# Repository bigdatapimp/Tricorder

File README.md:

This project is a compact hand held device based on the Arduino Nano 33 BLE sense Rev2 board, inspired by the Tricorder from the Star Trek Franchise
It utilzes a variety of on board sensors as well as GPS to gather a range of data.

There is no license to use this code. I would appriciate a mention if used in your own projects or if you choose to follow the build

By: Tony Dillberg
Feb 2026

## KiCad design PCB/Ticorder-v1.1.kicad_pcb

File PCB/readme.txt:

These are the current GERBER files for the PCB design, as well as the current version of the KiCAD files.

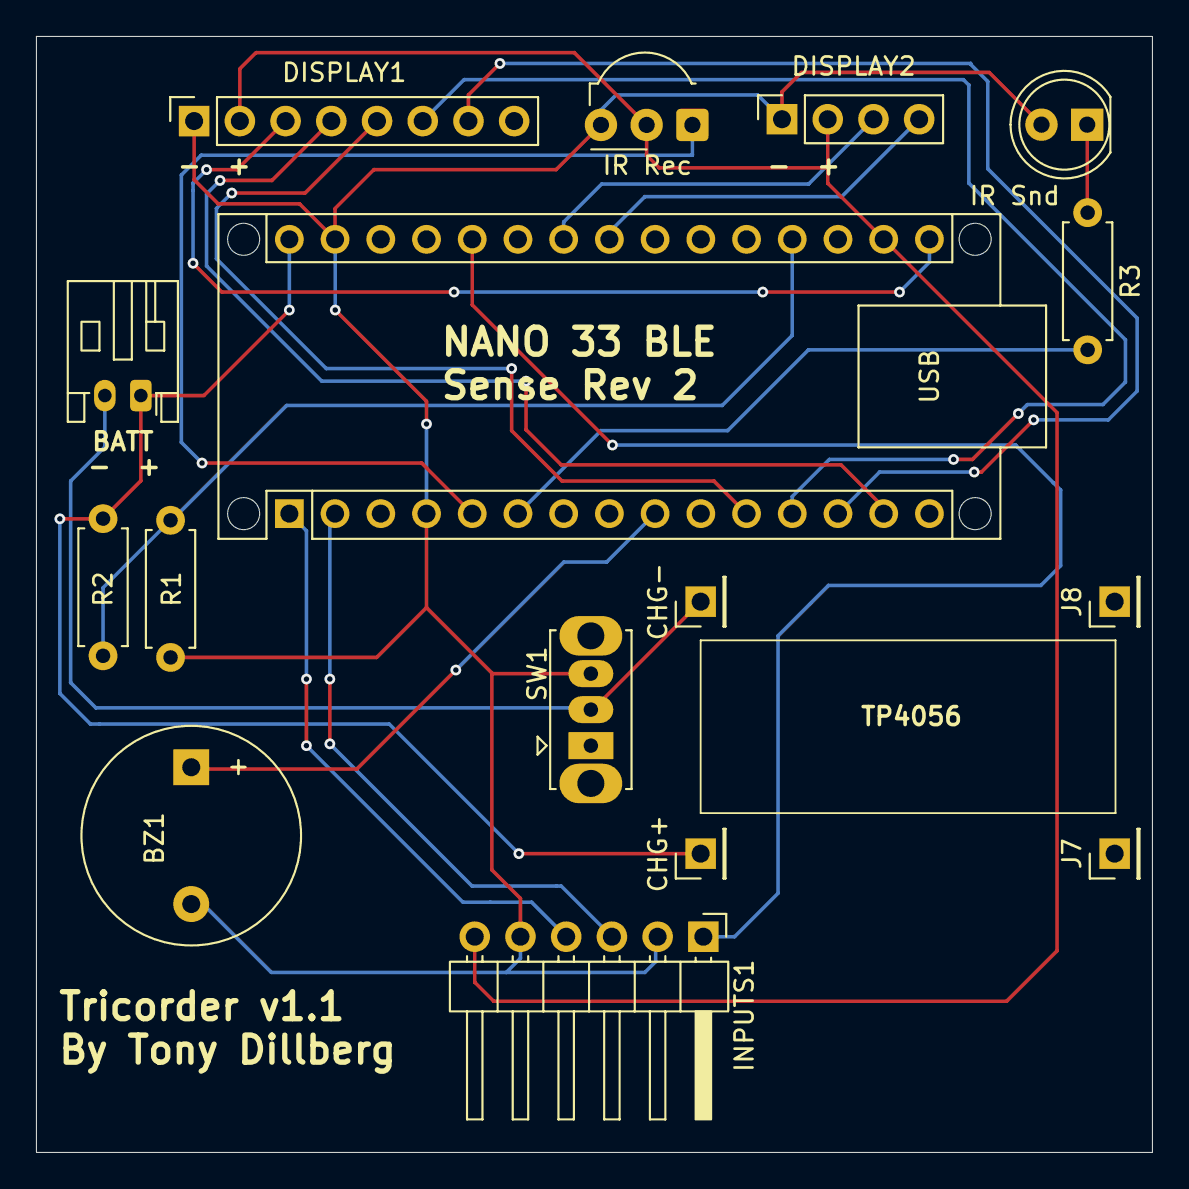
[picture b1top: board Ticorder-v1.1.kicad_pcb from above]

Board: 2 copper layers, 62.0 x 62.0 mm, 16 parts (0 on the bottom side), 19 nets.

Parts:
A1: Arduino_Nano_ESP32; Arduino_Nano_WithMountingHoles
BATT: Conn_01x02; JST_PH_S2B-PH-K_1x02_P2.00mm_Horizontal
BZ1: Buzzer; Buzzer_12x9.5RM7.6
CHG+: Conn_01x01_Pin; PinHeader_1x01_P2.54mm_Vertical
CHG-: Conn_01x01_Pin; PinHeader_1x01_P2.54mm_Vertical
DISPLAY1: Conn_01x08_Socket; PinSocket_1x08_P2.54mm_Vertical
DISPLAY2: Conn_01x04_Socket; PinSocket_1x04_P2.54mm_Vertical
INPUTS1: Conn_01x06_Pin; PinHeader_1x06_P2.54mm_Horizontal
IR Rec: VS1838B; Vishay_MOLD-3Pin
IR Snd: LD271; LED_D5.0mm_IRGrey
J7, J8: Conn_01x01_Pin; PinHeader_1x01_P2.54mm_Vertical
R1, R2: 10K; R_Axial_DIN0207_L6.3mm_D2.5mm_P7.62mm_Horizontal
R3: 220; R_Axial_DIN0207_L6.3mm_D2.5mm_P7.62mm_Horizontal
SW1: SW_SPDT; SW_Slide_SPDT_Straight_CK_OS102011MS2Q

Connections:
unnamed: A1.17 (3V3), DISPLAY1.2, DISPLAY2.2, INPUTS1.6, IR Rec.2 (Vs)
unnamed: A1.19 (A0), R1.2, R2.2
unnamed: A1.26 (A7), INPUTS1.1
unnamed: A1.2 (D0/RX), INPUTS1.3
unnamed: A1.1 (D1/TX), INPUTS1.4
unnamed: A1.5 (D2), IR Rec.1 (OUT)
unnamed: A1.6 (D3), R3.2
unnamed: A1.9 (D6), BZ1.1 (+)
unnamed: A1.11 (D8), DISPLAY1.5
unnamed: A1.12 (D9), DISPLAY1.6
unnamed: A1.13 (D10/CS), DISPLAY1.7
unnamed: A1.14 (D11/COPI), DISPLAY1.4
unnamed: A1.16 (D13/SCK), DISPLAY1.3
unnamed: A1.24 (SCL/A5), DISPLAY2.3
unnamed: A1.23 (SDA/A4), DISPLAY2.4
unnamed: A1.30 (VIN), BATT.1, CHG+.1, R1.1
unnamed: BATT.2, CHG-.1, SW1.2 (B)
unnamed: A1.4 (GND), A1.29 (GND), BZ1.2 (-), DISPLAY1.1, DISPLAY2.1, INPUTS1.2, INPUTS1.5, IR Rec.3 (GND), IR Snd.2 (A), R2.1, SW1.3 (C)
unnamed: IR Snd.1 (K), R3.1

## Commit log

2026-03-19 Rename tricorder_circuit_image.png to PCB/tricorder_circuit_image.png
2026-03-19 Rename Tricorder.step to PCB/Tricorder.step
2026-03-19 Rename Tricorder0.433.ino to Code/Tricorder0.433.ino
2026-03-19 Rename Tricorder0.432.ino to Code/Tricorder0.432.ino
2026-03-19 Rename Tricorder0.431.ino to Code/Tricorder0.431.ino
2026-03-19 Rename Tricorder0.42.ino to Code/Tricorder0.42.ino
2026-03-19 Rename Tricorder0.353.ino to Code/Tricorder0.353.ino
2026-03-19 Rename Tricorder0.352.ino to Code/Tricorder0.352.ino
2026-03-19 Rename Tricorder0.351.ino to Code/Tricorder0.351.ino
2026-03-19 Rename PinDefinitionsAndMore.h to Code/PinDefinitionsAndMore.h
2026-03-19 Rename Ticorder-v1.1.step to Ticorder-v1.1.step
2026-03-19 Rename Tricorder.step to Tricorder-v1.0.step
